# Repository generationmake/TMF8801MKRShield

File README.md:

# TMF8801MKRShield
Shield with ams TMF8801 1D time-of-flight sensor for Arduino MKR

## PCB

### Top

### Bottom

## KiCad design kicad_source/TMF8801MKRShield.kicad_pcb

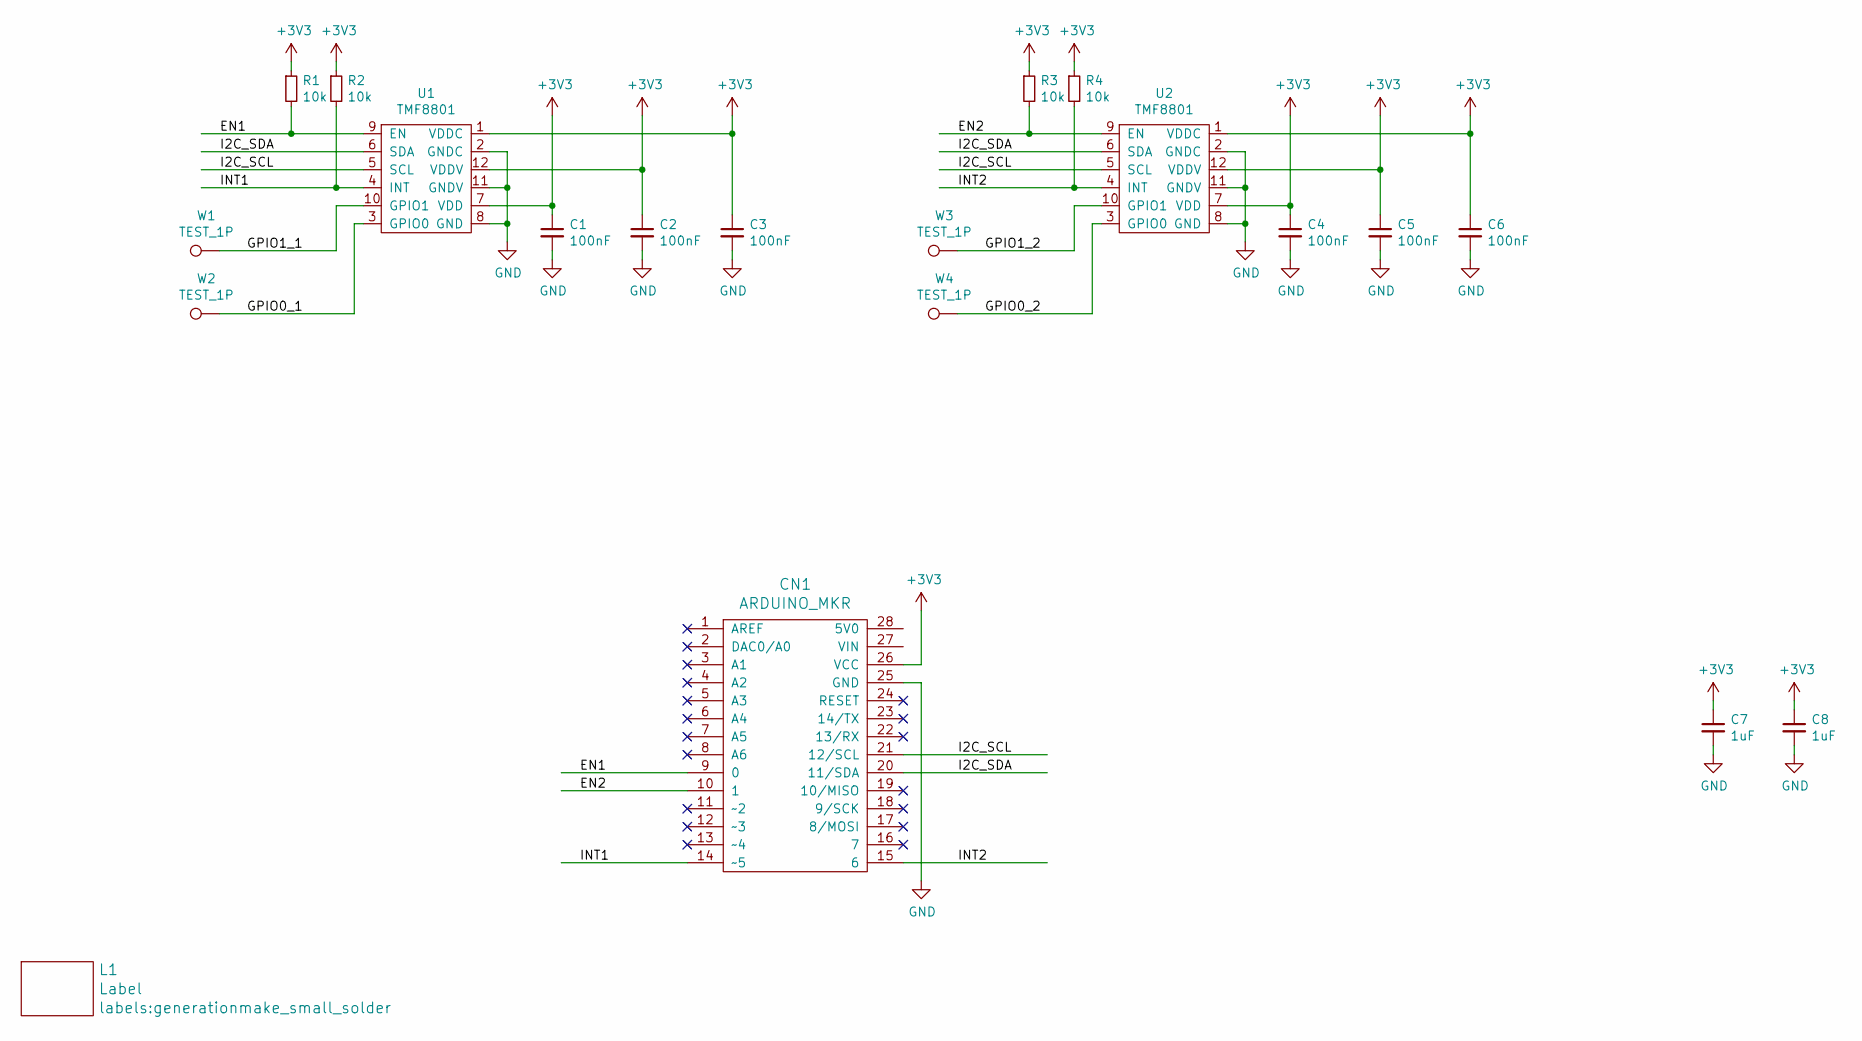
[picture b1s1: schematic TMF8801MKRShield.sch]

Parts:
C1, C2, C3, C4, C5, C6: 100nF; C_0603
C7, C8: 1uF; C_0603
CN1: ARDUINO_MKR; ARDUINO_MKR_HOLES_PINHEADER_EDGE
L1: Label; generationmake_small_solder
R1, R2, R3, R4: 10k; R_0603
U1, U2: TMF8801
W1, W2, W3, W4: TEST_1P; SolderWirePad_single_1mmSMD

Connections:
+3V3: C1.1, C2.1, C3.1, C4.1, C5.1, C6.1, C7.1, C8.1, CN1.26 (VCC), R1.1, R2.1, R3.1, R4.1, U1.1 (VDDC), U1.7 (VDD), U1.12 (VDDV), U2.1 (VDDC), U2.7 (VDD), U2.12 (VDDV)
/EN1: CN1.9 (0), R1.2, U1.9 (EN)
/EN2: CN1.10 (1), R3.2, U2.9 (EN)
/GPIO0_1: U1.3 (GPIO0), W2.1
/GPIO0_2: U2.3 (GPIO0), W4.1
/GPIO1_1: U1.10 (GPIO1), W1.1
/GPIO1_2: U2.10 (GPIO1), W3.1
/I2C_SCL: CN1.21 (12/SCL), U1.5 (SCL), U2.5 (SCL)
/I2C_SDA: CN1.20 (11/SDA), U1.6 (SDA), U2.6 (SDA)
/INT1: CN1.14 (~~5), R2.2, U1.4 (INT)
/INT2: CN1.15 (6), R4.2, U2.4 (INT)
GND: C1.2, C2.2, C3.2, C4.2, C5.2, C6.2, C7.2, C8.2, CN1.25 (GND), U1.2 (GNDC), U1.8 (GND), U1.11 (GNDV), U2.2 (GNDC), U2.8 (GND), U2.11 (GNDV)

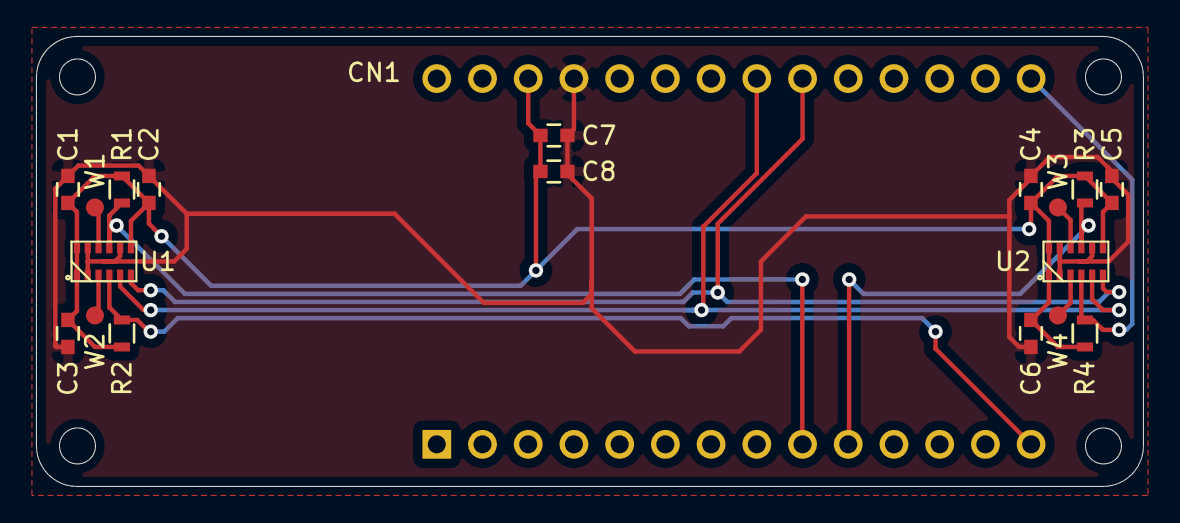
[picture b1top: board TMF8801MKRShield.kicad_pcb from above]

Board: 2 copper layers, 61.5 x 25.0 mm, 20 parts (0 on the bottom side), 12 nets.

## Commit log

2020-11-20 added kicad peoject
